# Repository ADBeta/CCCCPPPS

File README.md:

# Cheap Crappy Constant Current Portable Programmable Power Supply 
## A Power Supply built with a CH32V003

A DIY Programmable Buck/Boost Power Supply, with the following specs:  
* Max Output Voltage  15V
* Max Output Current  1.5A
* Max Output Power    5W

# Usage
## Debug Interface:
This interface is enabled by default when building the firmware. Use `minichlink`
to issue commands listed below

## USB Interface:
Build with `-DCONFIG_USE_USB`
> [!NOTE]
> To be implemented.

## Commands
> [!NOTE]
> Need to improve the command list and handler

- `0` to turn the supply off
- `1-9` to set the target Voltage/Current in multiples of 1000mV/100mA
- `c` to switch to Constant Current Mode 
- `v` to switch to Constant Voltage Mode
- `+` to increase the target Voltage/Current depending on mode, in 50mV/25mA increments
- ~~Konami code makes the unit self distruct.~~ Removed due to misuse.

# Build
```sh
export CH32V003FUN="path/to/ch32v003fun"
make
```

----
(c) 2024
Bogdan Ionescu
ADBeta

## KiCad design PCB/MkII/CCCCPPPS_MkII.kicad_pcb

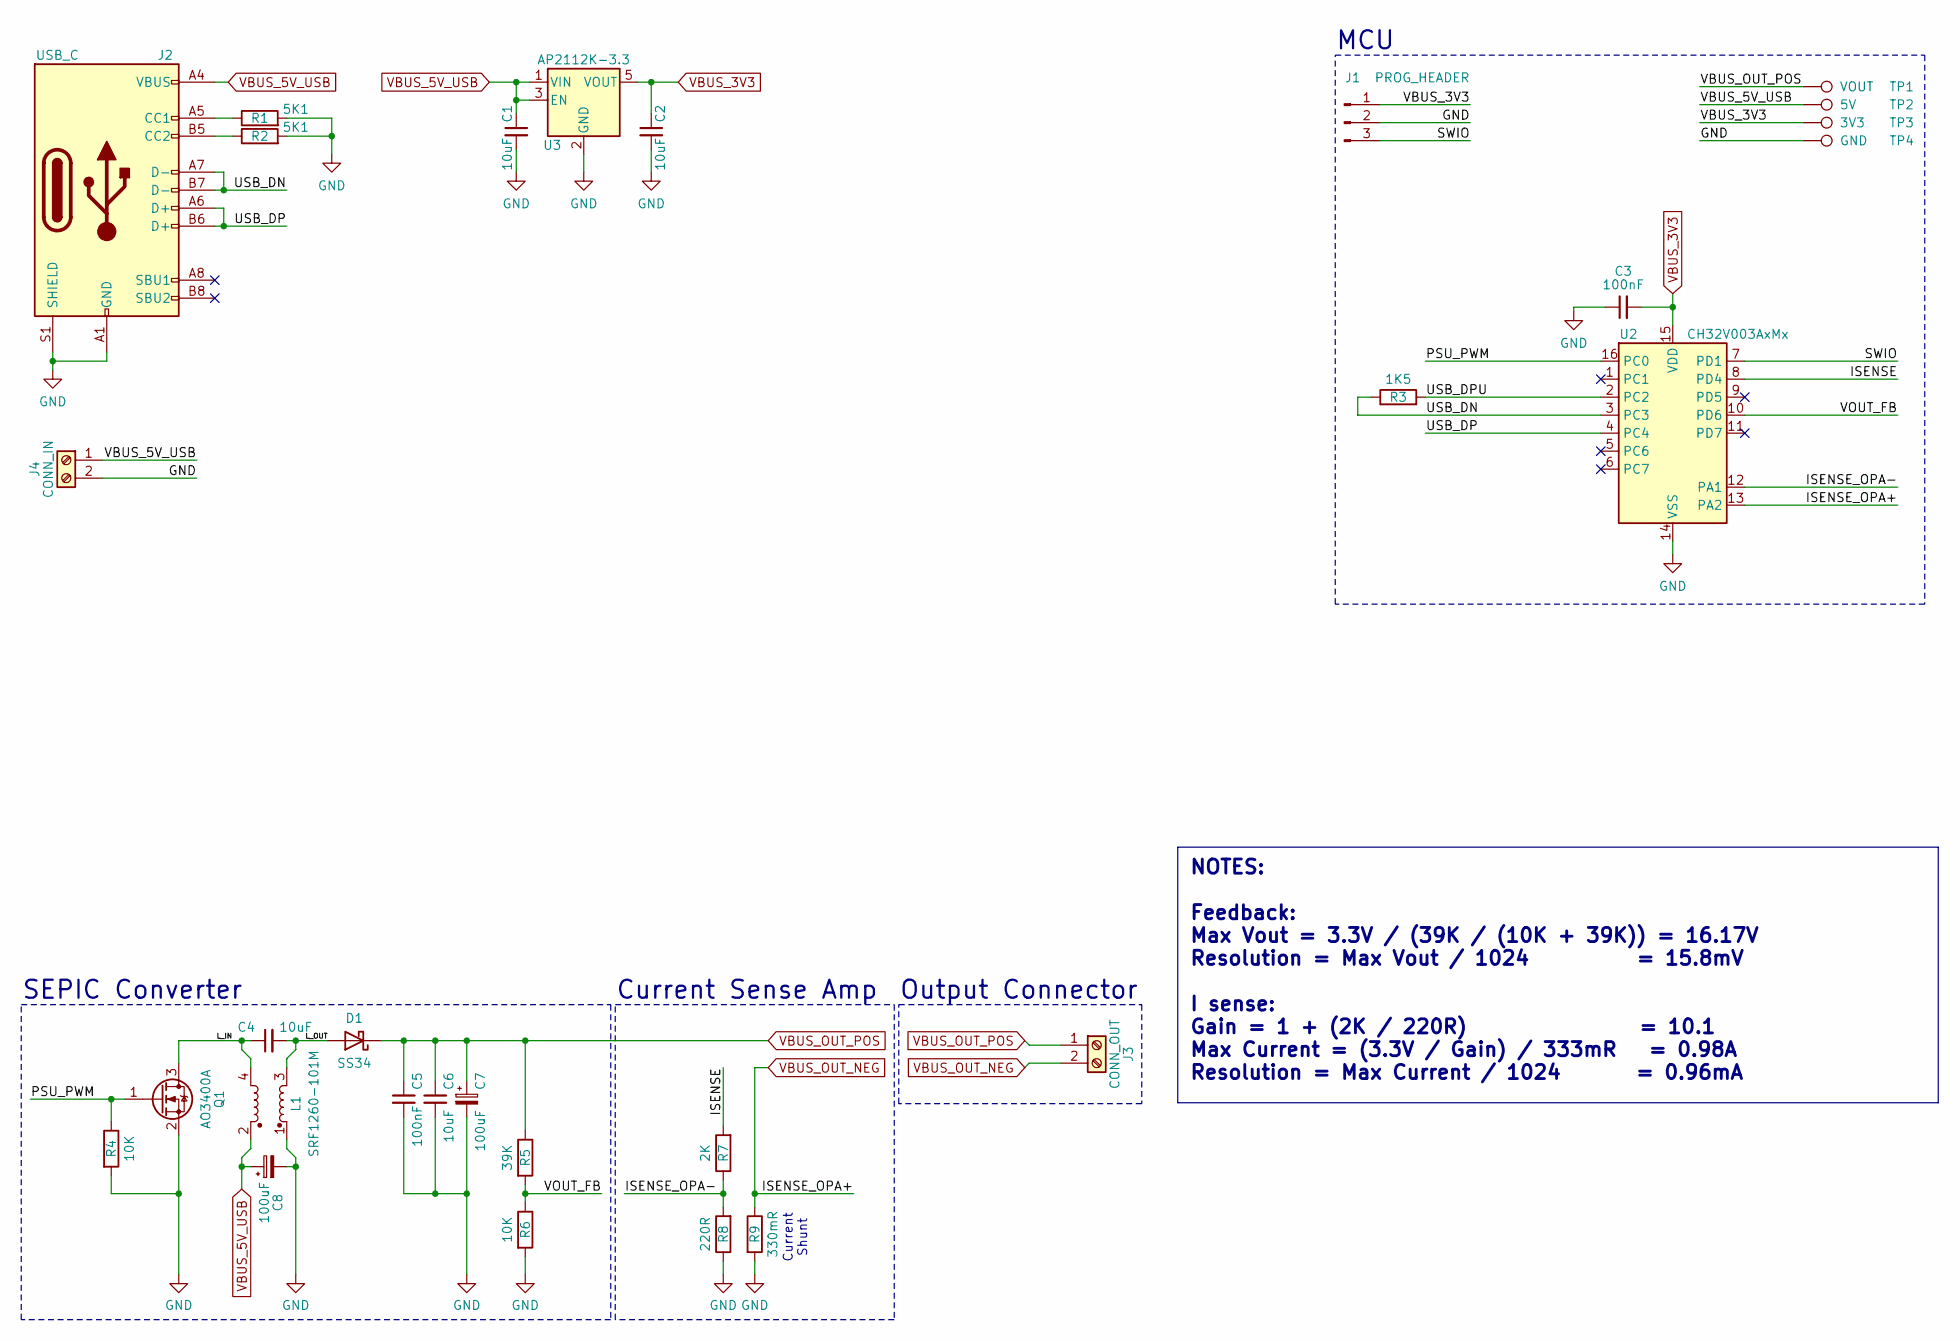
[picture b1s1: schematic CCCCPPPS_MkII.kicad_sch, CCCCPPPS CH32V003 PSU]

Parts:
C1, C2, C4, C6: 10uF; C_0805_2012Metric
C3, C5: 100nF; C_0805_2012Metric
C7, C8: 100uF; CP_Elec_6.3x5.2
D1: SS34; D_SMA
J1: PROG_HEADER; PinSocket_1x03_P2.54mm_Vertical
J2: USB_C; USB_C_Receptacle_G-Switch_GT-USB-7010ASV
J3: CONN_OUT; PCB_Terminal_Block_2-P3.5
J4: CONN_IN; PCB_Terminal_Block_2-P3.5
L1: SRF1260-101M; L_Bourns_SRF1260
Q1: AO3400A; SOT-23
R1, R2: 5K1; R_0805_2012Metric
R3: 1K5; R_0805_2012Metric
R4, R6: 10K; R_0805_2012Metric
R5: 39K; R_0805_2012Metric
R7: 2K; R_0805_2012Metric
R8: 220R; R_0805_2012Metric
R9: 330mR; R_2512_6332Metric_Pad1.40x3.35mm_HandSolder
TP1: VOUT; TestPoint_Pad_D3.0mm
TP2: 5V; TestPoint_Pad_D3.0mm
TP3: 3V3; TestPoint_Pad_D3.0mm
TP4: GND; TestPoint_Pad_D3.0mm
U2: CH32V003AxMx; SOP-16_3.9x9.9mm_P1.27mm
U3: AP2112K-3.3; SOT-23-5

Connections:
/ISENSE: R7.2, U2.8 (PD4)
/ISENSE_OPA-: R7.1, R8.2, U2.12 (PA1)
/L_IN: C4.1, L1.4, Q1.3 (D)
/L_OUT: C4.2, D1.2 (A), L1.3
/PSU_PWM: Q1.1 (G), R4.1, U2.16 (PC0)
/SWIO: J1.3, U2.7 (PD1)
/USB_DN: J2.A7 (D-), J2.B7 (D-), R3.1, U2.3 (PC3)
/USB_DP: J2.A6 (D+), J2.B6 (D+), U2.4 (PC4)
/USB_DPU: R3.2, U2.2 (PC2)
/VOUT_FB: R5.2, R6.1, U2.10 (PD6)
GND: C1.2, C2.2, C3.1, C5.2, C6.2, C7.2, C8.2, J1.2, J2.A1 (GND), J2.A12 (GND), J2.B1 (GND), J2.B12 (GND), J2.S1 (SHIELD), J4.2, L1.1, Q1.2 (S), R1.2, R2.2, R4.2, R6.2, R8.1, R9.2, TP4.1, U2.14 (VSS), U3.2 (GND)
unnamed: J2.A5 (CC1), R1.1
unnamed: J2.B5 (CC2), R2.1
VBUS_3V3: C2.1, C3.2, J1.1, TP3.1, U2.15 (VDD), U3.5 (VOUT)
VBUS_5V_USB: C1.1, C8.1, J2.A4 (VBUS), J2.A9 (VBUS), J2.B4 (VBUS), J2.B9 (VBUS), J4.1, L1.2, TP2.1, U3.1 (VIN), U3.3 (EN)
VBUS_OUT_NEG: J3.2, R9.1, U2.13 (PA2)
VBUS_OUT_POS: C5.1, C6.1, C7.1, D1.1 (K), J3.1, R5.1, TP1.1

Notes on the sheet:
NOTES: Feedback: Max Vout = 3.3V / (39K / (10K + 39K)) = 16.17V Resolution = Max Vout / 1024 = 15.8mV I sense: Gain = 1 + (2K / 220R) = 10.1 Max Current = (3.3V / Gain) / 333mR = 0.98A Resolution = Max Current / 1024 = 0.96mA
MCU
Output Connector
Current Shunt
SEPIC Converter
Current Sense Amp

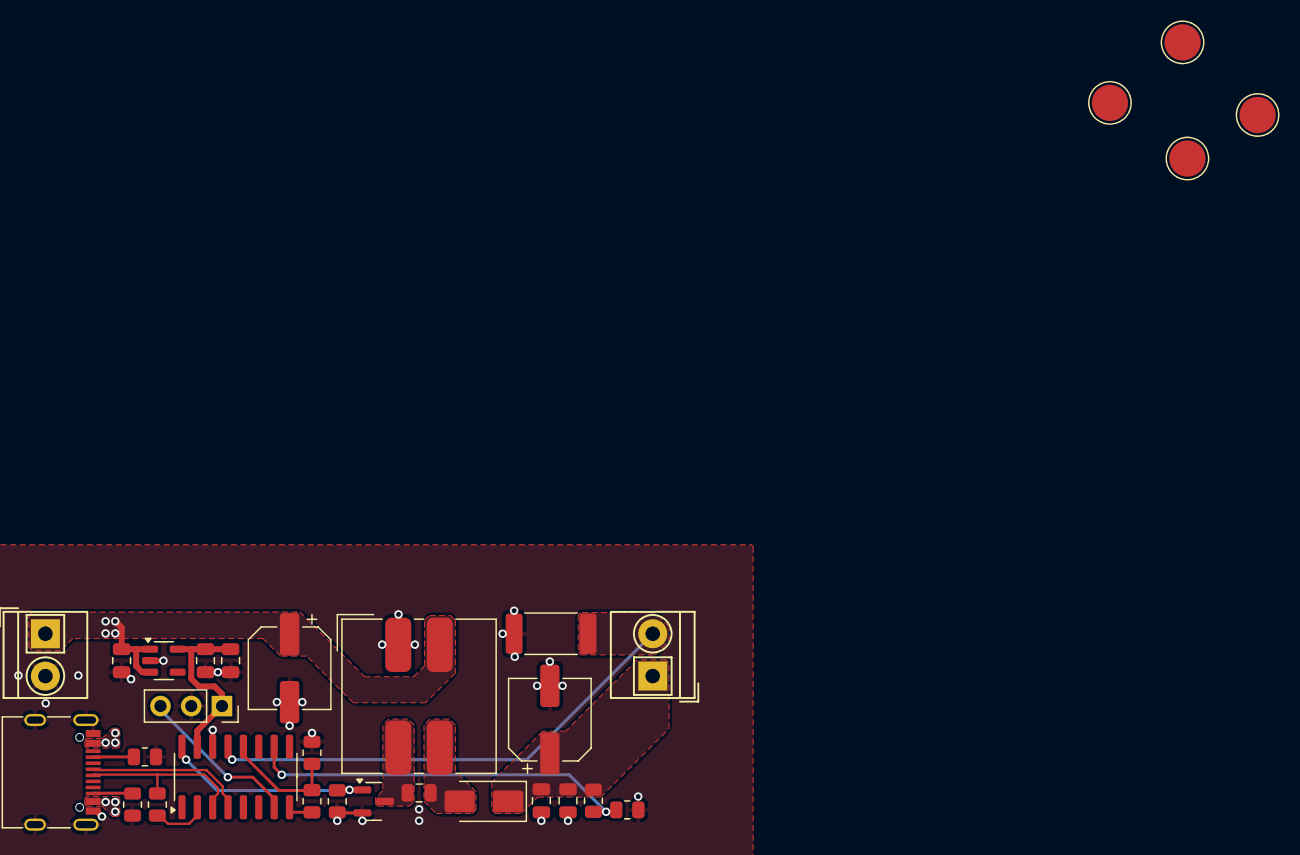
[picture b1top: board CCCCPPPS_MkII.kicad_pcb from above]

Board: 2 copper layers, 30 parts (0 on the bottom side), 17 nets.

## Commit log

2024-10-31 Fixed Type : Added info (TBD)
2024-10-31 Updated rv003usb and added commands header
2024-10-31 Changed Manufacturer and Unit string
2024-10-31 Reformat directory tree
2024-11-01 MkII PCB Started
2024-11-08 MkII PCB Update
2024-11-09 PCB Near final
2024-11-14 Full Refactor
